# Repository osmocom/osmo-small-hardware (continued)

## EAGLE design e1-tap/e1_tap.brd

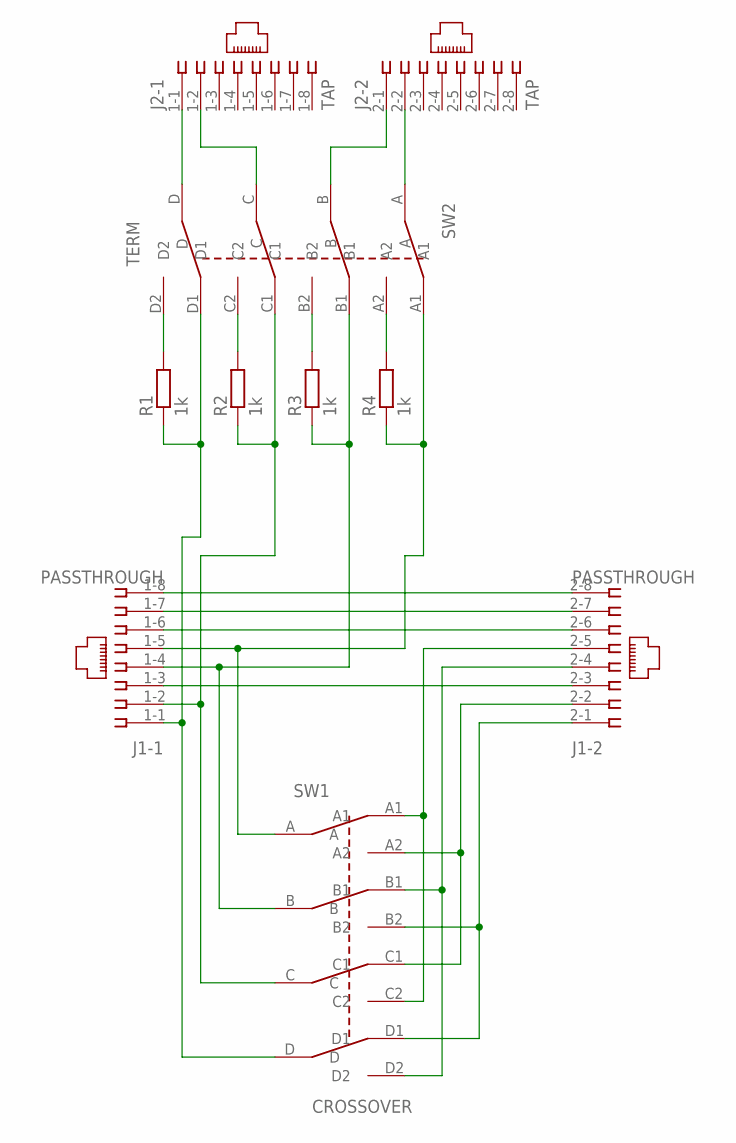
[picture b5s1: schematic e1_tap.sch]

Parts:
J1: PASSTHROUGH; 557560-1; MANUFACTURERPARTNUMBER 5557560-1
J2: TAP; 557560-1; MANUFACTURERPARTNUMBER 5557560-1
R1, R2, R3, R4: 1k; R0603; MANUFACTURERPARTNUMBER RC0603FR-071KL
SW1: CROSSOVER; 4PDT_DIL12; MANUFACTURERPARTNUMBER 1-1825010-3
SW2: TERM; 4PDT_DIL12; MANUFACTURERPARTNUMBER 1-1825010-3

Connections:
CROSS: J1.2-4 (4), SW1.B1, SW1.D2
unnamed: J1.1-8 (8), J1.2-8 (8)
unnamed: J1.1-7 (7), J1.2-7 (7)
unnamed: J1.1-6 (6), J1.2-6 (6)
unnamed: J1.1-3 (3), J1.2-3 (3)
unnamed: J1.1-2 (2), R2.1, SW1.C, SW2.C1
unnamed: J1.1-1 (1), R1.1, SW1.D, SW2.D1
unnamed: J1.1-4 (4), R3.1, SW1.B, SW2.B1
unnamed: J1.1-5 (5), R4.1, SW1.A, SW2.A1
unnamed: J1.2-5 (5), SW1.A1, SW1.C2
unnamed: J2.1-1 (1), SW2.D
unnamed: J1.2-2 (2), SW1.A2, SW1.C1
unnamed: J1.2-1 (1), SW1.B2, SW1.D1
unnamed: J2.1-2 (2), SW2.C
unnamed: J2.2-1 (1), SW2.B
unnamed: J2.2-2 (2), SW2.A
unnamed: R1.2, SW2.D2
unnamed: R2.2, SW2.C2
unnamed: R3.2, SW2.B2
unnamed: R4.2, SW2.A2

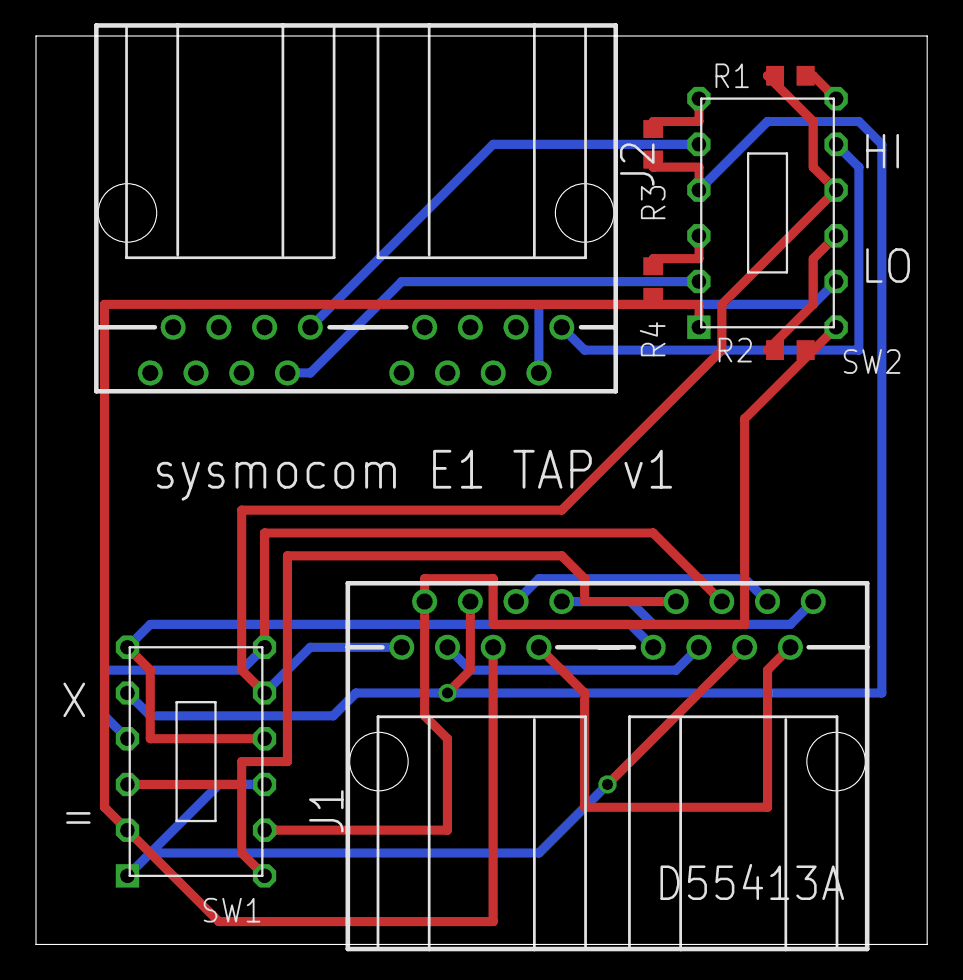
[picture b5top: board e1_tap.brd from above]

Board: 2 copper layers, 49.5 x 50.5 mm, 8 parts (0 on the bottom side), 20 nets.

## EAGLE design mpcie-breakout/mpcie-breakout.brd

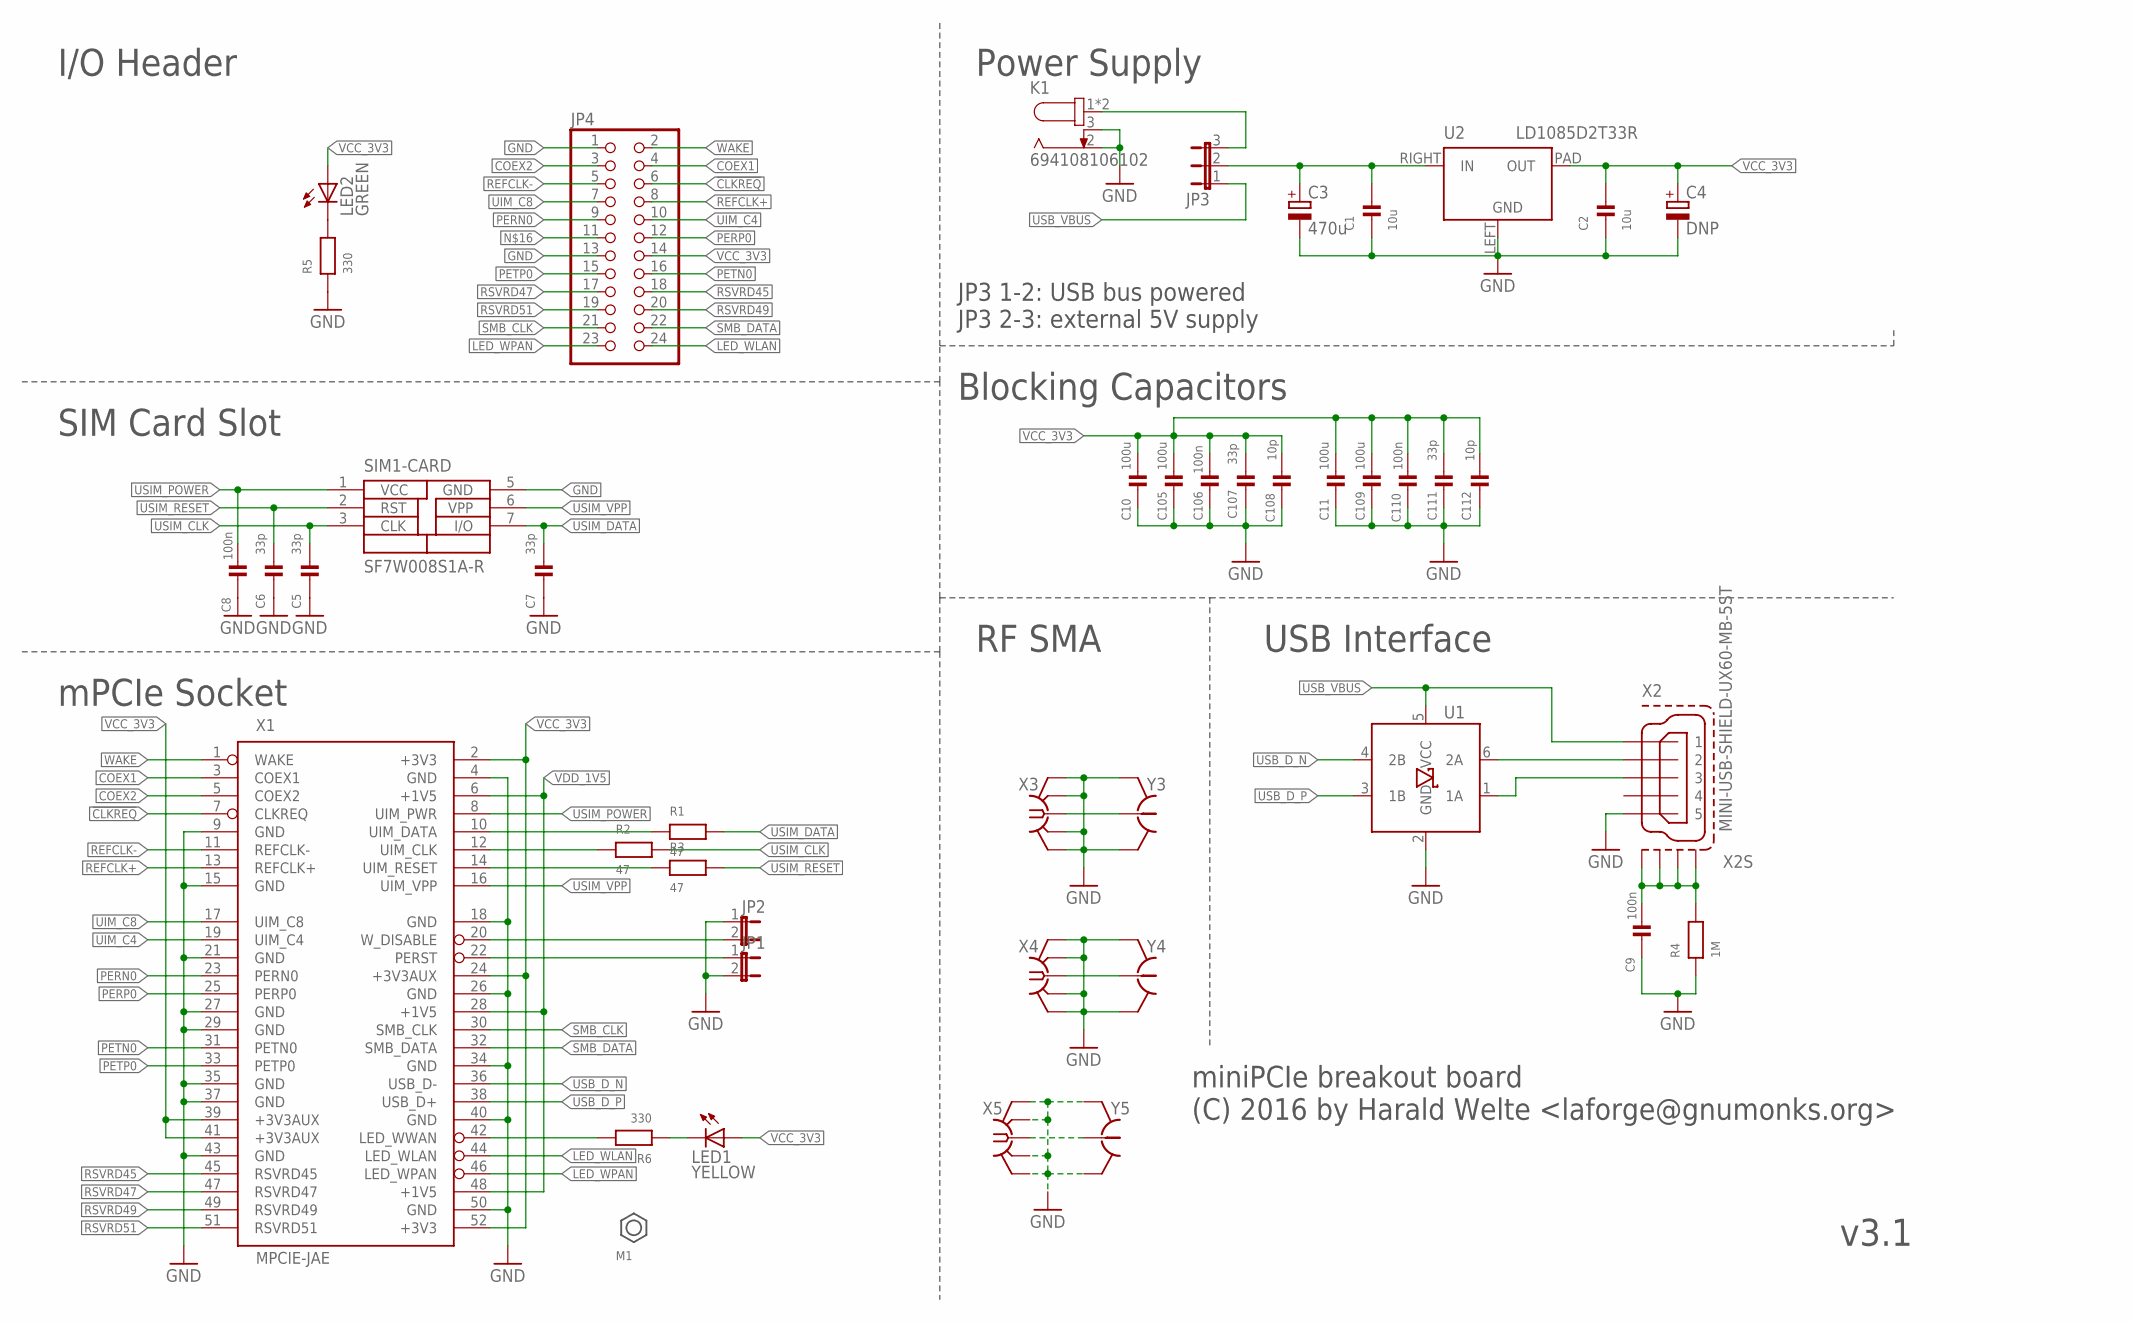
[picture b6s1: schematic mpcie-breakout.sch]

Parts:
C1, C2: 10u; _0805; MANUFACTURERPARTNUMBER CL21A106KOQNNNG
C3: 470u; UD-8X10_NICHICON; MANUFACTURERPARTNUMBER UUR0J471MNL1GS
C4: DNP; SMC_E; MANUFACTURERPARTNUMBER UNKNOWN MANUFACTURER PART NUMBER
C5, C6, C7, C107, C111: 33p; _0402; MANUFACTURERPARTNUMBER CL05C330JB5NNNC
C8, C9, C106, C110: 100n; _0603; MANUFACTURERPARTNUMBER CL10B104KO8NNNC
C10, C11, C105, C109: 100u; 1206; MANUFACTURERPARTNUMBER GRM31CR60J107ME39K
C108, C112: 10p; _0603; MANUFACTURERPARTNUMBER C0603C100J5GACTU
JP1, JP2: JP1E; JP1; MANUFACTURERPARTNUMBER UNKNOWN MANUFACTURER PART NUMBER
JP3: JP2E; JP2; MANUFACTURERPARTNUMBER UNKNOWN MANUFACTURER PART NUMBER
JP4: PINHD-2X12; 2X12; MANUFACTURERPARTNUMBER 961224-6404-AR
K1: 694108106102; MANUFACTURERPARTNUMBER 694108106102
LED1: YELLOW; CHIP-LED0603; MANUFACTURERPARTNUMBER UNKNOWN MANUFACTURER PART NUMBER
LED2: GREEN; CHIP-LED0603; MANUFACTURERPARTNUMBER UNKNOWN MANUFACTURER PART NUMBER
R1, R2, R3: 47; _0603; MANUFACTURERPARTNUMBER RC0603JR-0747RL
R4: 1M; _0603; MANUFACTURERPARTNUMBER RC0603JR-071ML
R5, R6: 330; _0603; MANUFACTURERPARTNUMBER RC0603JR-07330RL
SIM1: SF7W008S1A-R; SF7W008S1A-RESTR; MANUFACTURERPARTNUMBER SF7W008S1AE900
U1: IP4234CZ6; TSOP-6; MANUFACTURERPARTNUMBER IP4234CZ6,125
U2: LD1085D2T33R; ST_D2PAK; MANUFACTURERPARTNUMBER LD1085D2T33R
X1: MPCIE-JAE; MM60-52; MANUFACTURERPARTNUMBER MM60-52B1-E1-R650
X2: MINI-USB-SHIELD-UX60-MB-5ST; UX60-MB-5ST; MANUFACTURERPARTNUMBER UX60-MB-5ST
X3, X4, X5: SMA-F-S-TH; MANUFACTURERPARTNUMBER 5-1814832-1
Y3, Y4, Y5: HRS_UFL; MANUFACTURERPARTNUMBER U.FL-R-SMT(01)

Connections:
!CLKREQ: JP4.6, X1.7 (CLKREQ)
COEX1: JP4.4, X1.3 (COEX1)
COEX2: JP4.3, X1.5 (COEX2)
GND: C1.1, C2.1, C3.-, C4.-, C5.2, C6.2, C7.2, C8.1, C9.1, C10.1, C11.1, C105.1, C106.1, C107.2, C108.2, C109.1, C110.1, C111.2, C112.2, JP1.2, JP2.1, JP4.1, JP4.13, K1.2, K1.3, R4.1, R5.1, SIM1.5 (GND), U1.2 (GND), U2.LEFT (GND), X1.4 (GND), X1.9 (GND), X1.15 (GND), X1.18 (GND), X1.21 (GND), X1.26 (GND), X1.27 (GND), X1.29 (GND), X1.34 (GND), X1.35 (GND), X1.37 (GND), X1.40 (GND), X1.43 (GND), X1.50 (GND), X2.5, X3.G1 (GND), X3.G2 (GND), X3.G3 (GND), X3.G4 (GND), X4.G1 (GND), X4.G2 (GND), X4.G3 (GND), X4.G4 (GND), X5.G1 (GND), X5.G2 (GND), X5.G3 (GND), X5.G4 (GND), Y3.GND@1 (GND), Y3.GND@2 (GND), Y4.GND@1 (GND), Y4.GND@2 (GND), Y5.GND@1 (GND), Y5.GND@2 (GND)
LDO_IN: C1.2, C3.+, JP3.2, U2.RIGHT (IN)
LED_WLAN: JP4.24, X1.44 (LED_WLAN)
LED_WPAN: JP4.23, X1.46 (LED_WPAN)
unnamed: LED2.C, R5.2
unnamed: LED1.C, R6.1
unnamed: R6.2, X1.42 (LED_WWAN)
unnamed: R1.1, X1.10 (UIM_DATA)
unnamed: X5.C (1), Y5.SIG (1)
unnamed: R2.1, X1.12 (UIM_CLK)
unnamed: R3.1, X1.14 (UIM_RESET)
unnamed: C9.2, R4.2, X2.M1 (S1), X2.M2 (S2), X2.M3 (S3), X2.M4 (S4)
unnamed: JP3.3, K1.1, K1.1-1 (1)
unnamed: X3.C (1), Y3.SIG (1)
unnamed: X4.C (1), Y4.SIG (1)
PERN0: JP4.9, X1.23 (PERN0)
PERP0: JP4.12, X1.25 (PERP0)
PERST: JP1.1, X1.22 (PERST)
PETN0: JP4.16, X1.31 (PETN0)
PETP0: JP4.15, X1.33 (PETP0)
REFCLK+: JP4.8, X1.13 (REFCLK+)
REFCLK-: JP4.5, X1.11 (REFCLK-)
RSVRD45: JP4.18, X1.45 (RSVRD45)
RSVRD47: JP4.17, X1.47 (RSVRD47)
RSVRD49: JP4.20, X1.49 (RSVRD49)
RSVRD51: JP4.19, X1.51 (RSVRD51)
SMB_CLK: JP4.21, X1.30 (SMB_CLK)
SMB_DATA: JP4.22, X1.32 (SMB_DATA)
UIM_C4: JP4.10, X1.19 (UIM_C4)
UIM_C8: JP4.7, X1.17 (UIM_C8)
USB_D_N: U1.4 (2B), X1.36 (USB_D-)
USB_D_P: U1.3 (1B), X1.38 (USB_D+)
USB_VBUS: JP3.1, U1.5 (VCC), X2.1
USIM_CLK: C5.1, R2.2, SIM1.3 (CLK)
USIM_DATA: C7.1, R1.2, SIM1.7 (I/O)
USIM_POWER: C8.2, SIM1.1 (VCC), X1.8 (UIM_PWR)
USIM_RESET: C6.1, R3.2, SIM1.2 (RST)
USIM_VPP: SIM1.6 (VPP), X1.16 (UIM_VPP)
VCC_3V3: C2.2, C4.+, C10.2, C11.2, C105.2, C106.2, C107.1, C108.1, C109.2, C110.2, C111.1, C112.1, JP4.14, LED1.A, LED2.A, U2.PAD (OUT), X1.2 (+3V3), X1.24 (+3V3AUX), X1.39 (+3V3AUX), X1.41 (+3V3AUX), X1.52 (+3V3)
VDD_1V5: X1.6 (+1V5), X1.28 (+1V5), X1.48 (+1V5)
WAKE: JP4.2, X1.1 (WAKE)
W_DISABLE: JP2.2, X1.20 (W_DISABLE)
_USB_D_N: U1.6 (2A), X2.2
_USB_D_P: U1.1 (1A), X2.3

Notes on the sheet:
miniPCIe breakout board (C) 2016 by Harald Welte <laforge@gnumonks.org>
I/O Header
SIM Card Slot
mPCIe Socket
Power Supply
Blocking Capacitors
USB Interface
JP3 1-2: USB bus powered JP3 2-3: external 5V supply
RF SMA

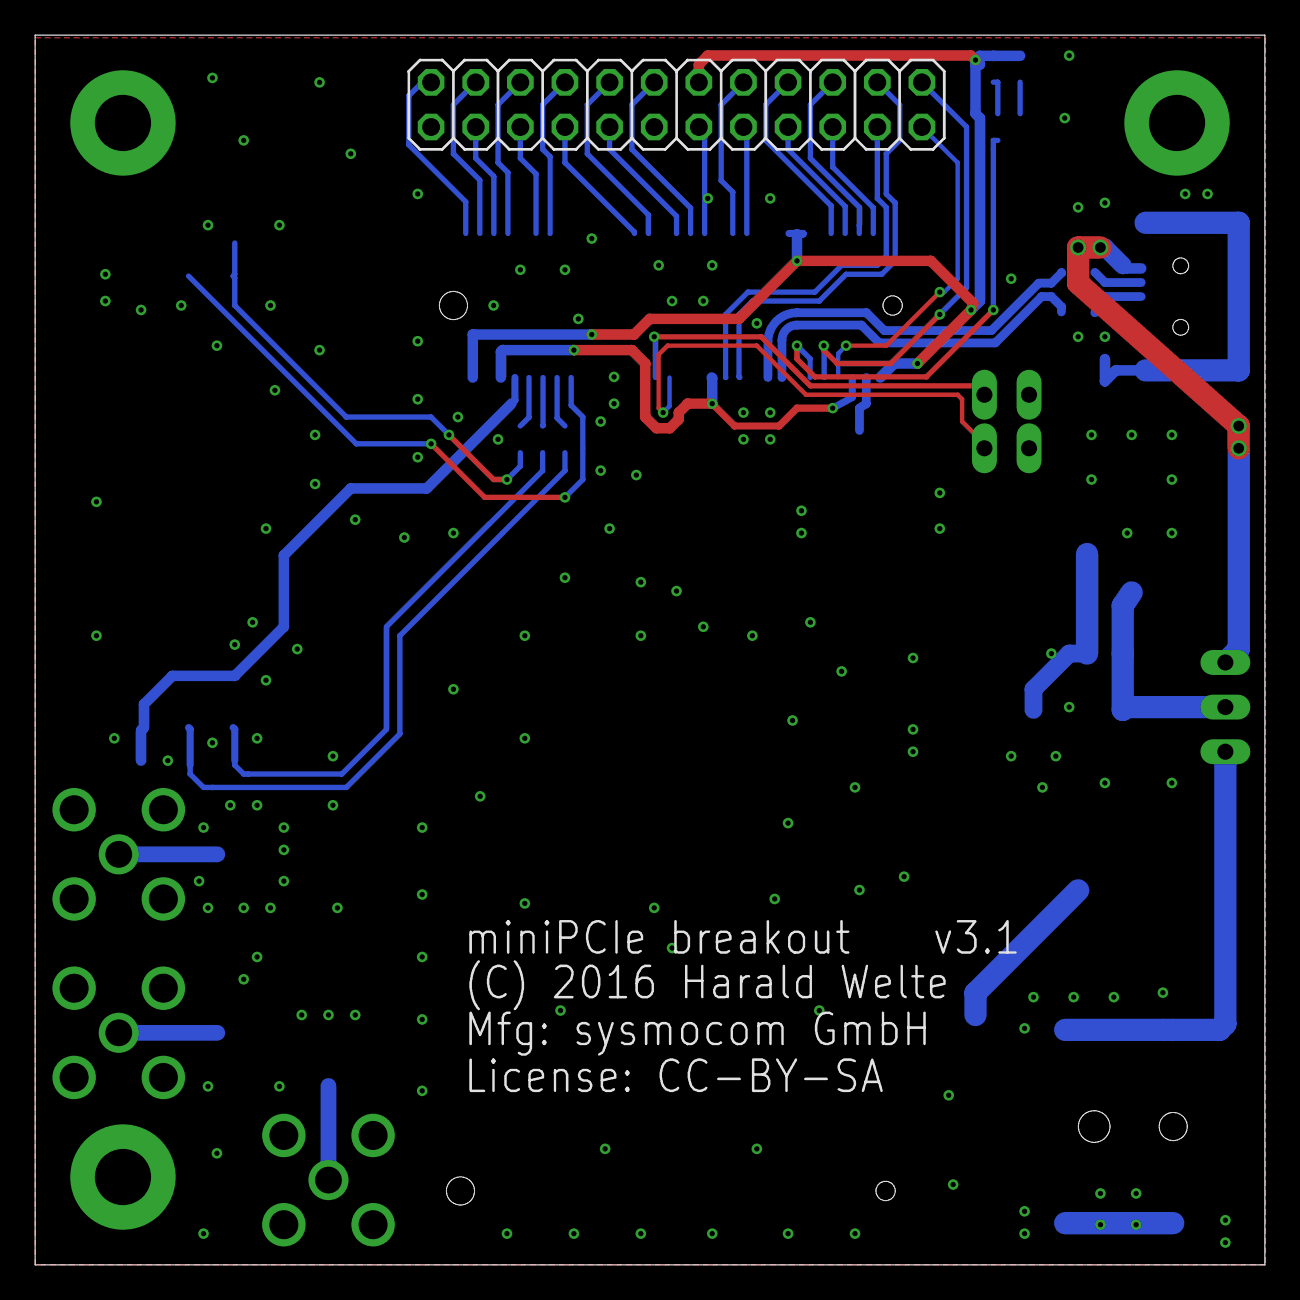
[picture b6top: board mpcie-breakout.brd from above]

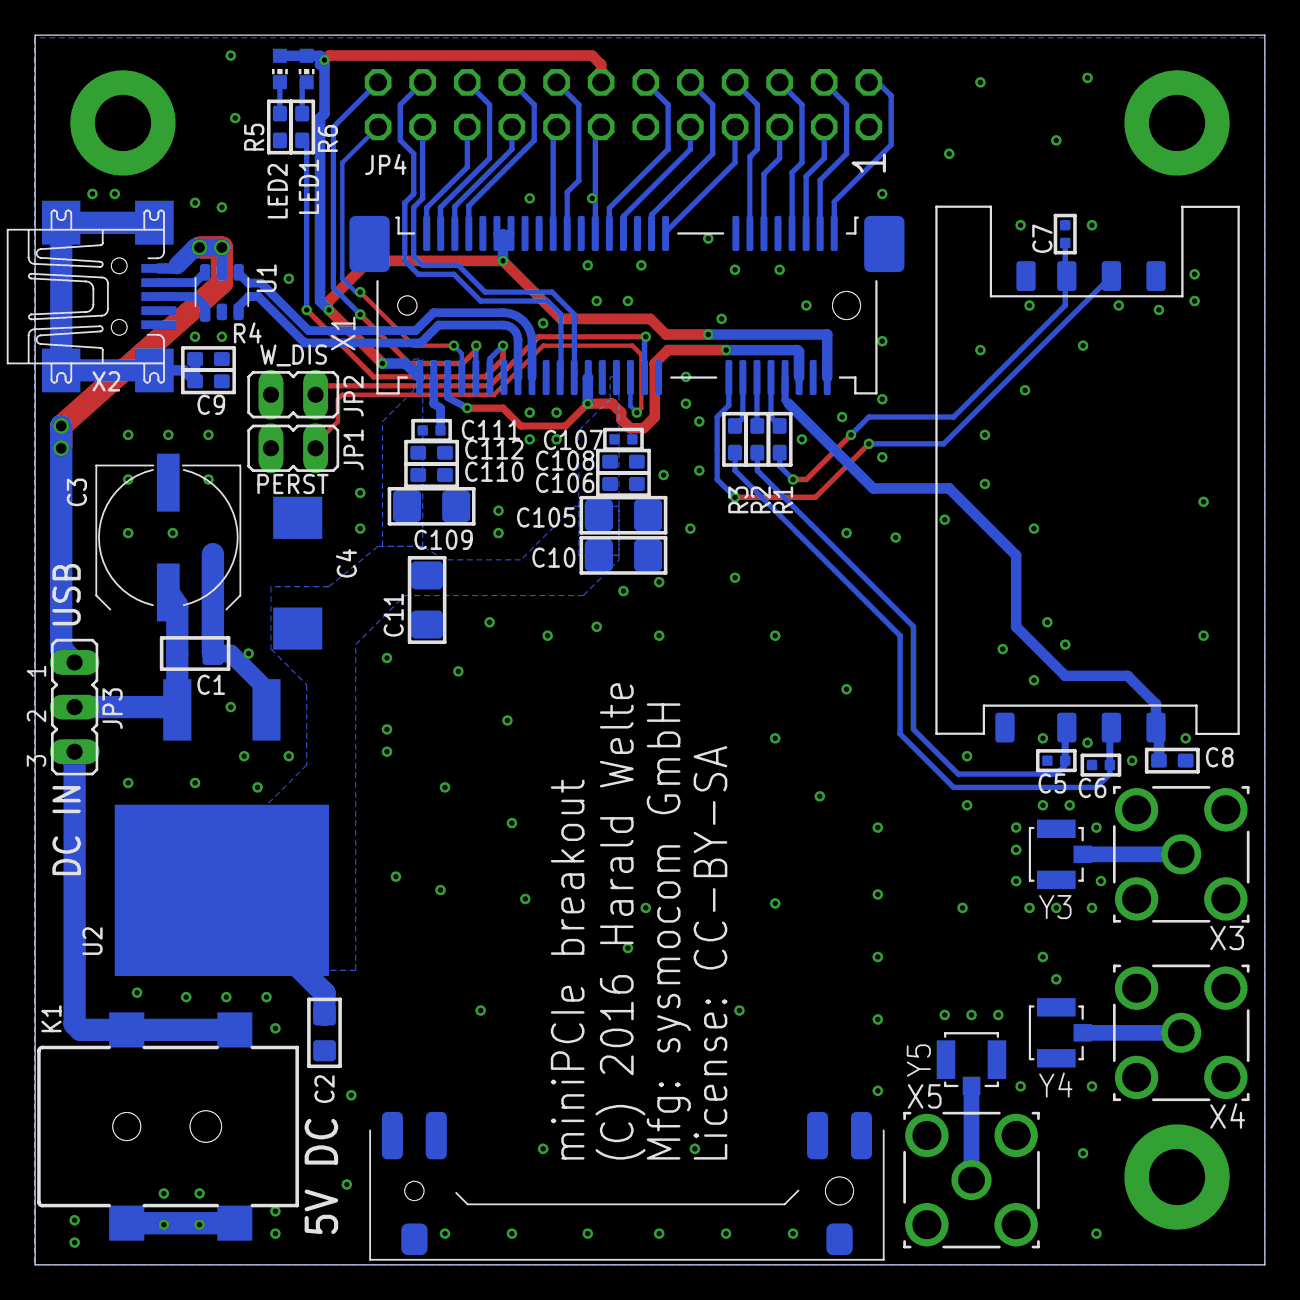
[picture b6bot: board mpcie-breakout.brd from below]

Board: 2 copper layers, 70.0 x 70.0 mm, 43 parts (42 on the bottom side), 47 nets.
